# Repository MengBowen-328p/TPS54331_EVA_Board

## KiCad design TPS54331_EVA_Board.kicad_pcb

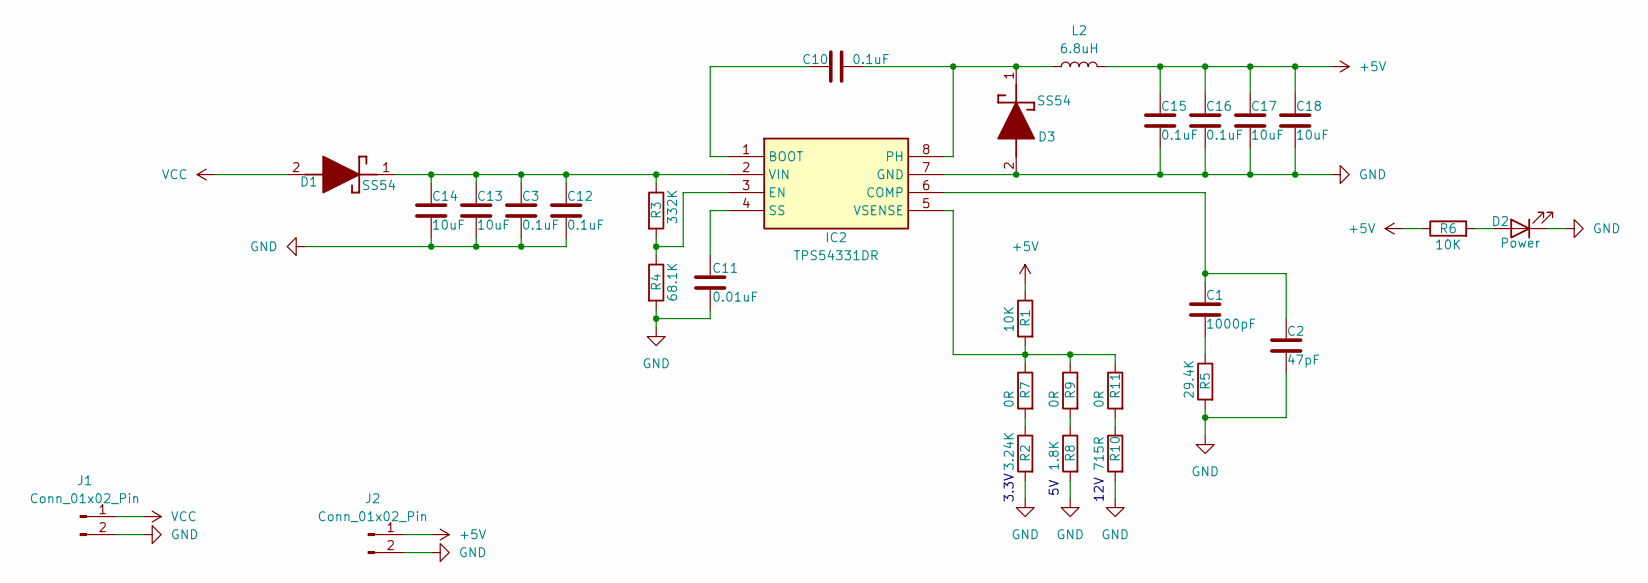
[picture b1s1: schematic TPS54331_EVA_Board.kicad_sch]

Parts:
C1: 1000pF; C_0603_1608Metric
C2: 47pF; C_0603_1608Metric
C3, C12, C15, C16: 0.1uF; C_1206_3216Metric
C10: 0.1uF; C_0603_1608Metric
C11: 0.01uF; C_0603_1608Metric
C13, C14, C17, C18: 10uF; C_1206_3216Metric
D1, D3: SS54; DIOM5126X245N; Manufacturer_Part_Number SS54
D2: Power; LED_0603_1608Metric
IC2: TPS54331DR; SOIC127P600X175-8N; Manufacturer_Part_Number TPS54331DR; Mouser Part Number 595-TPS54331DR
J1, J2: Conn_01x02_Pin; Power_PAD
L2: 6.8uH; L_Changjiang_FNR5040S
R1, R6: 10K; R_0603_1608Metric
R2: 3.24K; R_0603_1608Metric
R3: 332K; R_0603_1608Metric
R4: 68.1K; R_0603_1608Metric
R5: 29.4K; R_0603_1608Metric
R7, R9, R11: 0R; R_0603_1608Metric
R8: 1.8K; R_0603_1608Metric
R10: 715R; R_0603_1608Metric

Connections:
+5V: C15.1, C16.1, C17.1, C18.1, J2.1, L2.2, R1.1, R6.1
GND: C2.2, C3.2, C11.1, C12.2, C13.2, C14.2, C15.2, C16.2, C17.2, C18.2, D2.1 (K), D3.2 (A), IC2.7 (GND), J1.2, J2.2, R2.2, R4.2, R5.2, R8.2, R10.2
unnamed: C1.2, R5.1
unnamed: C3.1, C12.1, C13.1, C14.1, D1.1 (K), IC2.2 (VIN), R3.1
unnamed: D2.2 (A), R6.2
unnamed: C10.2, D3.1 (K), IC2.8 (PH), L2.1
unnamed: C10.1, IC2.1 (BOOT)
unnamed: C1.1, C2.1, IC2.6 (COMP)
unnamed: IC2.3 (EN), R3.2, R4.1
unnamed: C11.2, IC2.4 (SS)
unnamed: IC2.5 (VSENSE), R1.2, R7.1, R9.1, R11.1
unnamed: R2.1, R7.2
unnamed: R8.1, R9.2
unnamed: R10.1, R11.2
VCC: D1.2 (A), J1.1

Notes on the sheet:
12V
3.3V

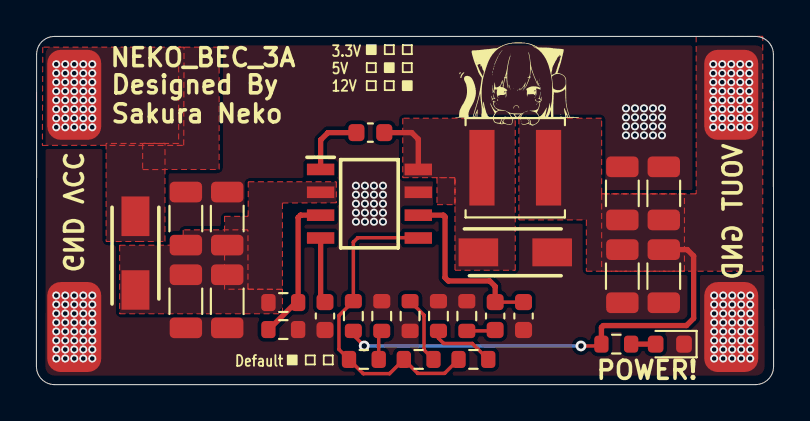
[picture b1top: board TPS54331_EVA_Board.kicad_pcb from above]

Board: 2 copper layers, 40.9 x 19.3 mm, 30 parts (0 on the bottom side), 15 nets.

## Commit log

2024-10-16 Update LCEDA Project
